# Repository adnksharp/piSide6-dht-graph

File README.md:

# Read temperature and humidity with DHT sensors

Medir temperatura y humedad del ambiente usando sensores de temperatura DHT, Arduino y Python

## Requisitos

### En arduino

#### Instalar [FirmataExpress](https://github.com/MrYsLab/FirmataExpress)
<details>
  <summary>En arduino-cli</summary>
  
```
arduino lib install --git-url https://github.com/MrYsLab/FirmataExpress.git
```

> Es necesario tener activa la opción `enable_unsafe_install` del archivo de [configuración de Arduino-cli](https://arduino.github.io/arduino-cli/0.20/configuration/)

</details>
<details>
  <summary>En arduino IDE</summary>

https://mryslab.github.io/pymata4/firmata_express/#installation-instructions
  
</details>

#### Cargar el [proyecto de FirmataExpress](https://github.com/MrYsLab/FirmataExpress) a la placa de Arduino

### Librerías de Python

- PySide6
- matplotlib
- pymata4

```bash
pip install -r requirements.txt
```

### Hardware usado

|  |  |
|----|----|

- Placa de Arduino MEGA 2560
- Sensor DHT11

## Características
- Mostrar la humedad (%) y la temperatura en (°C y °F) dentro de labels.
- Graficar la temperatura.

### En proceso

> [!TIP]
>
> Graficar la humedad.

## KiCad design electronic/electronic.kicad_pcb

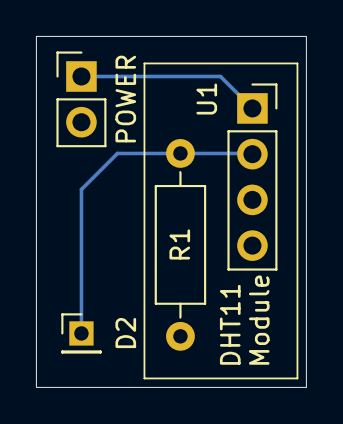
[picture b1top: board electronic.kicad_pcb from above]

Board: 2 copper layers, 15.0 x 19.5 mm, 4 parts (0 on the bottom side), 3 nets.

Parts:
J1: POWER; PinHeader_1x02_P2.54mm_Vertical
J2: D2; PinHeader_1x01_P2.00mm_Vertical
R1: 10k; R_Axial_DIN0207_L6.3mm_D2.5mm_P10.16mm_Horizontal
U1: DHT11; PinSocket_1x04_P2.54mm_Vertical

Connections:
+5V: J1.1, U1.1 (VDD)
D2: J2.1, R1.1, U1.2 (DATA)
GNDREF: J1.2, R1.2, U1.4 (GND)

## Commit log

2024-12-08 chore: init.
2024-12-08 style: form defined.
2024-12-08 feat: get dht data from arduino.
2024-12-08 docs: Update README.md
2024-12-08 feat: display data.
2024-12-09 chore: kidad electronic design added.
2024-12-10 chore: kidad electronic design modified.
